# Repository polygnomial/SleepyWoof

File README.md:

# SleepyWoof

PCB for radiation testing the Oresat watchdog timer circuit, using the non-SEP version of the TLV1704 quad comparator

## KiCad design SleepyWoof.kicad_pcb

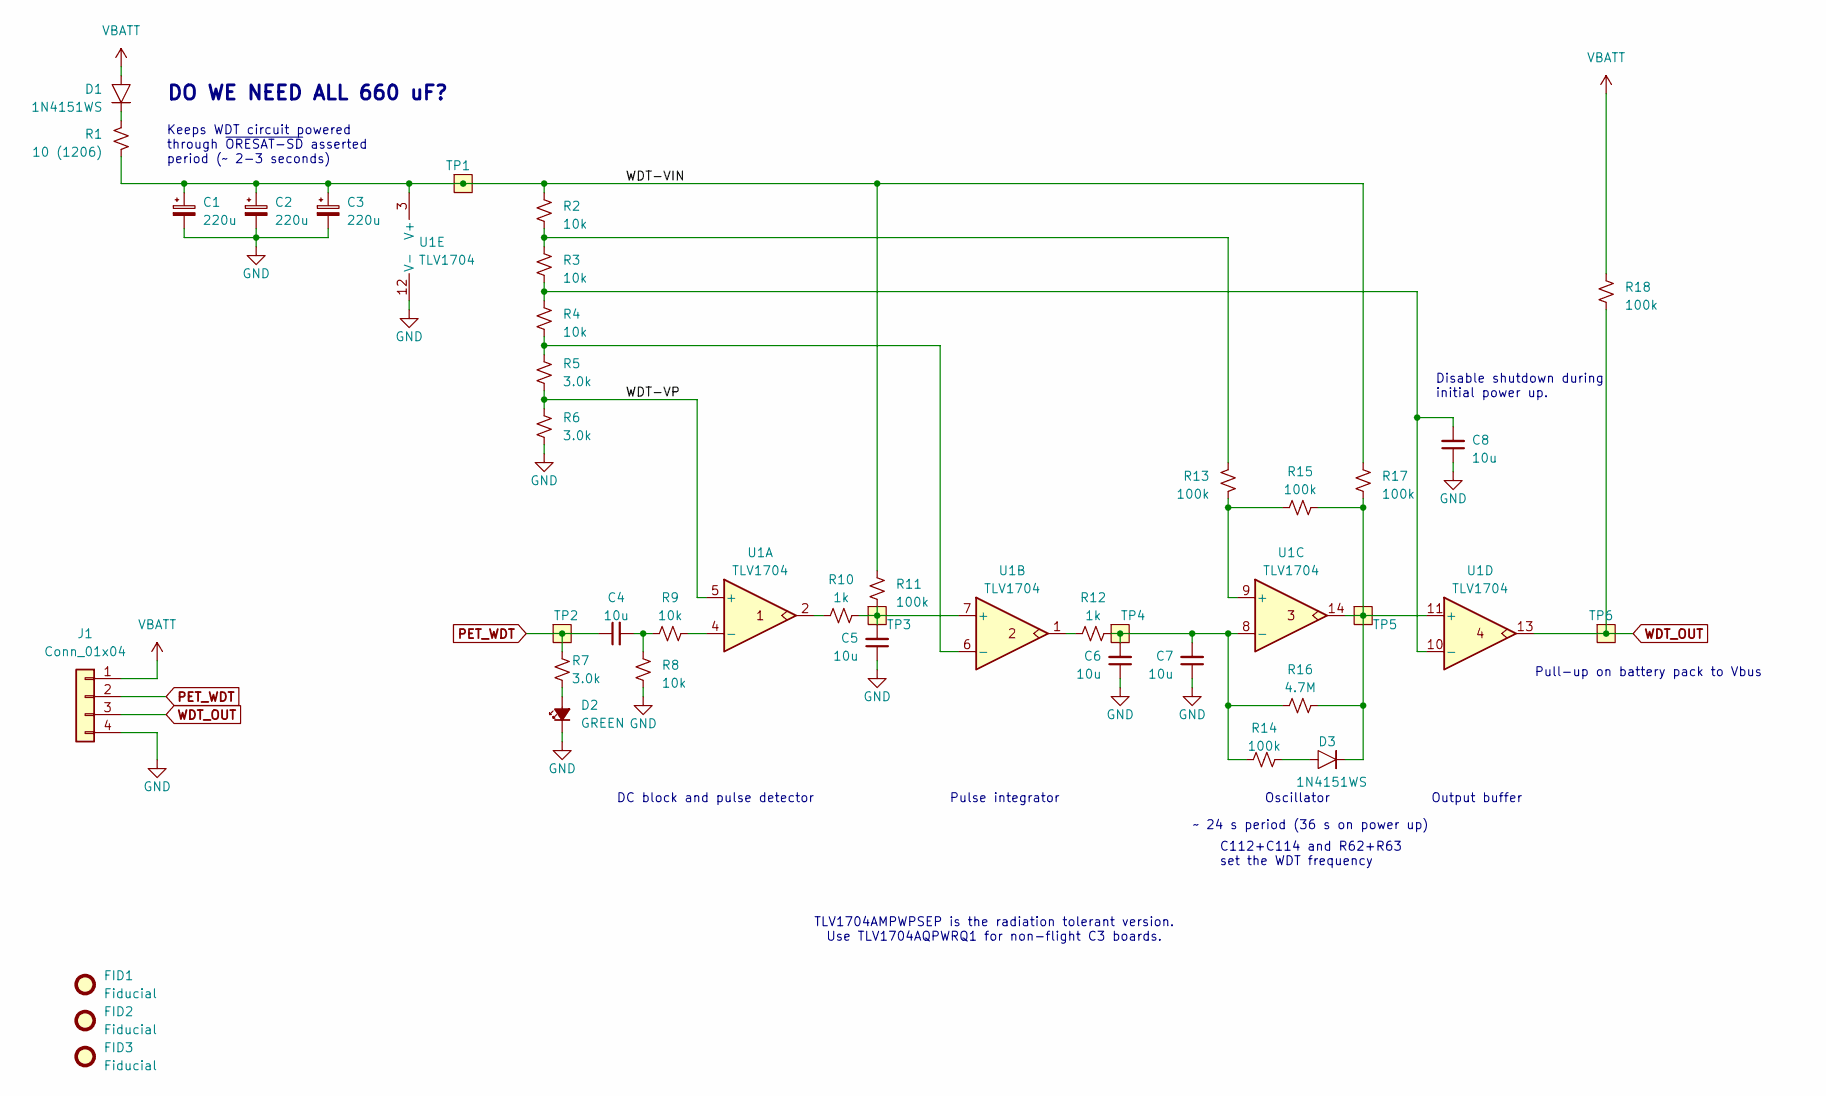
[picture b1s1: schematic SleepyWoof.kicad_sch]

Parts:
C1, C2, C3: 220u; CP_EIA-7361-38_AVX-V; MPN TCN4227M025R0100
C4, C5, C6, C7, C8: 10u; C_0603_1608Metric; MPN GRT188R61C106KE13D
D1, D3: 1N4151WS; D_SOD-323; MPN 1N4151WS-E3-08
D2: GREEN; LED_0603_1608Metric; MPN 150060GS75000
FID1, FID2, FID3: Fiducial; Fiducial_1mm_Mask2mm
J1: Conn_01x04; PinHeader_1x04_P2.54mm_Vertical
R1: 10 (1206); R_1206_3216Metric; MPN ESR18EZPF10R0
R2, R3, R4, R8, R9: 10k; R_0603_1608Metric; MPN RMCF0603FT10K0
R5, R6, R7: 3.0k; R_0603_1608Metric; MPN RMCF0603FT3K00
R10, R12: 1k; R_0603_1608Metric; MPN RMCF0603FT1K00
R11, R13, R14, R15, R17, R18: 100k; R_0603_1608Metric; MPN RMCF0603FT100K
R16: 4.7M; R_0603_1608Metric; MPN RMCF0603FT4M70
TP1, TP2, TP3, TP4, TP5, TP6: TestPoint-MinTH; TestPoint-0.75mm-th
U1: TLV1704; TSSOP-14_4.4x5mm_P0.65mm; MPN TLV1704AQPWRQ1

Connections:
/WDT-VIN: C1.1, C2.1, C3.1, R1.2, R2.1, R11.1, R17.2, TP1.1, U1.3 (V+)
/WDT-VP: R5.2, R6.1, U1.5 (+)
GND: C1.2, C2.2, C3.2, C5.1, C6.1, C7.1, C8.1, D2.1 (K), J1.4, R6.2, R8.2, U1.12 (V-)
unnamed: C4.2, R8.1, R9.1
unnamed: D1.1, R1.1
unnamed: D2.2 (A), R7.2
unnamed: D3.2, R14.1
unnamed: R10.1, U1.2
unnamed: R12.1, U1.1
unnamed: R2.2, R3.1, R13.2
unnamed: R9.2, U1.4 (-)
unnamed: C5.2, R10.2, R11.2, TP3.1, U1.7 (+)
unnamed: R4.2, R5.1, U1.6 (-)
unnamed: R13.1, R15.1, U1.9 (+)
unnamed: C6.2, C7.2, R12.2, R14.2, R16.2, TP4.1, U1.8 (-)
unnamed: D3.1, R15.2, R16.1, R17.1, TP5.1, U1.11 (+), U1.14
unnamed: C8.2, R3.2, R4.1, U1.10 (-)
PET_WDT: C4.1, J1.2, R7.1, TP2.1
VBATT: D1.2, J1.1, R18.2
WDT_OUT: J1.3, R18.1, TP6.1, U1.13

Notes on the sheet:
Pulse integrator
Output buffer
Oscillator
C112+C114 and R62+R63 set the WDT frequency
TLV1704AMPWPSEP is the radiation tolerant version. Use TLV1704AQPWRQ1 for non-flight C3 boards.
Pull-up on battery pack to Vbus
DO WE NEED ALL 660 uF?
DC block and pulse detector
Disable shutdown during initial power up.
Keeps WDT circuit powered through ~{ORESAT-SD} asserted period (~ 2-3 seconds)
~ 24 s period (36 s on power up)

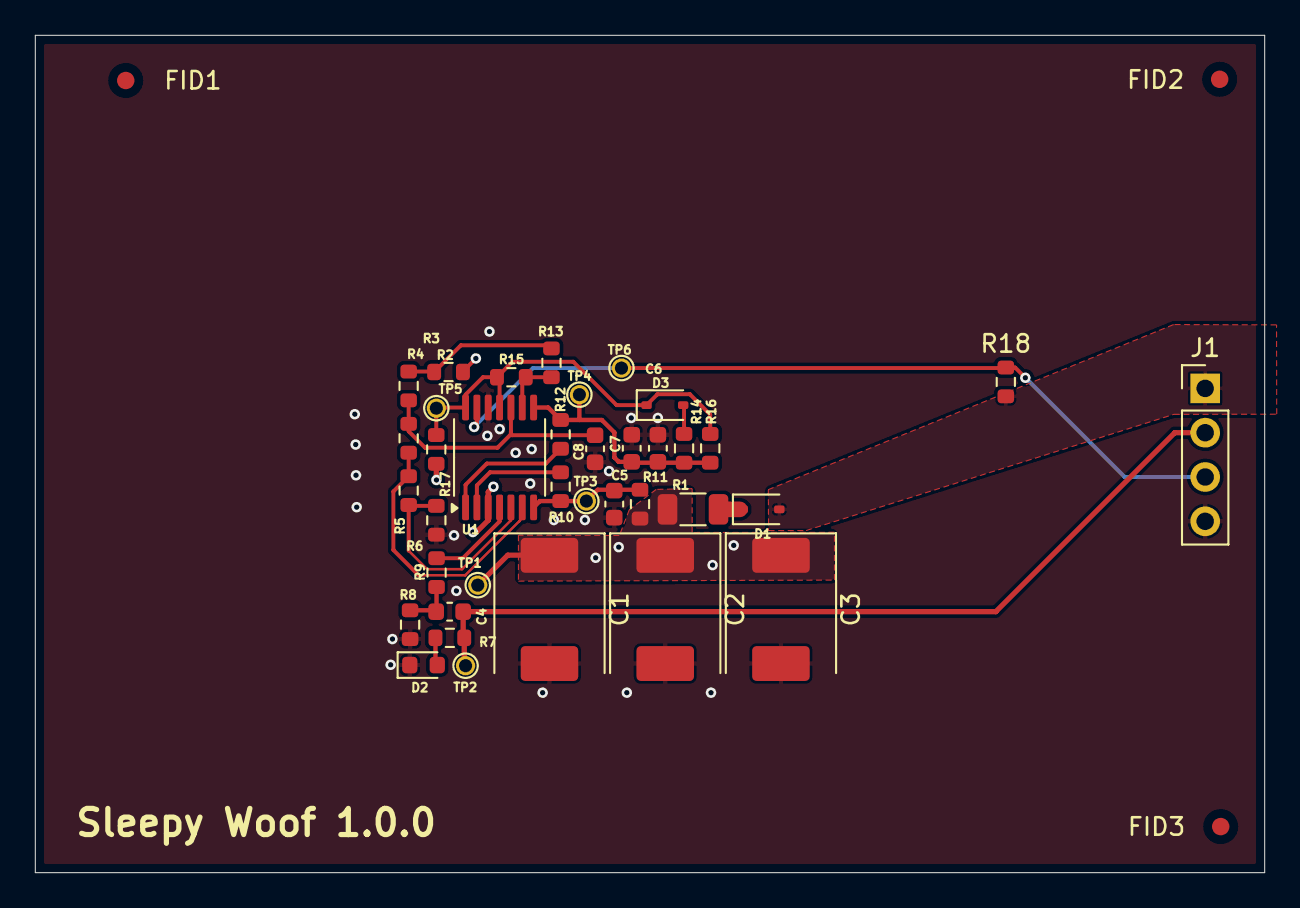
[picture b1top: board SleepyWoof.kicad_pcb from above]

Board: 2 copper layers, 70.5 x 48.0 mm, 40 parts (0 on the bottom side), 20 nets.

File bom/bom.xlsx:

null | Sourced | Placed | References | Value | Footprint | MFR | MPN | DPN | DST | Quantity
1 |  |  | C4, C5, C6, C7, C8 | 10u | C_0603_1608Metric | Murata | GRT188R61C106KE13D | 490-12317-1-ND | Digi-Key | 5
2 |  |  | C1, C2, C3 | 220u | CP_EIA-7361-38_AVX-V | Kyocera AVX | TCN4227M025R0100 | 478-12518-2-ND | Digi-Key | 3
3 |  |  | R11, R13, R14, R15, R17, R18 | 100k | R_0603_1608Metric | Stackpole Electronics Inc | RMCF0603FT100K | RMCF0603FT100KCT-ND | Digi-Key | 6
4 |  |  | R2, R3, R4, R8, R9 | 10k | R_0603_1608Metric | Stackpole Electronics Inc | RMCF0603FT10K0 | RMCF0603FT10K0CT-ND | Digi-Key | 5
5 |  |  | R5, R6, R7 | 3.0k | R_0603_1608Metric | Stackpole Electronics Inc | RMCF0603FT3K00 | RMCF0603FT3K00CT-ND | Digi-Key | 3
6 |  |  | R10, R12 | 1k | R_0603_1608Metric | Stackpole Electronics Inc | RMCF0603FT1K00 | RMCF0603FT1K00CT-ND | Digi-Key | 2
7 |  |  | R1 | 10 (1206) | R_1206_3216Metric | Rohm Semiconductor | ESR18EZPF10R0 | RHM10.0AFCT-ND | Digi-Key | 1
8 |  |  | R16 | 4.7M | R_0603_1608Metric | Stackpole Electronics Inc | RMCF0603FT4M70 | RMCF0603FT4M70CT-ND | Digi-Key | 1
9 |  |  | D1, D3 | 1N4151WS | D_SOD-323 | Vishay | 1N4151WS-E3-08 | 112-1N4151WS-E3-08CT-ND | Digi-Key | 2
10 |  |  | D2 | GREEN | LED_0603_1608Metric | Wurth | 150060GS75000 | 732-4971-1-ND | Digi-Key | 1
11 |  |  | U1 | TLV1704 | TSSOP-14_4.4x5mm_P0.65mm | Texas Instruments | TLV1704AQPWRQ1 | 296-43799-2-ND | Digi-Key | 1
12 |  |  | J1 | Conn_01x04 | PinHeader_1x04_P2.54mm_Vertical |  |  |  |  | 1

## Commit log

2024-08-15 routing tweaks
2024-08-15 ordered!
